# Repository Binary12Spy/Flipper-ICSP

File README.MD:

# Flipper-ICSP

Shout out to [Speexvocon](https://github.com/Speexvocon) for his [FlipperZeroKiCadPart](https://github.com/Speexvocon/FlipperZeroKiCadPart) making this project a whole lot easier!

I wanted to make a module for the Flipper Zero that works with [AVR Flasher](https://lab.flipper.net/apps/avr_isp) and simplifies hooking up a AVR microcontroller for flashing.  
This module simply formats the pins used by AVR Flasher into standard 10 position and 6 position ICSP headers with the option to choose between 3v3, 5v, or no supplied voltage.

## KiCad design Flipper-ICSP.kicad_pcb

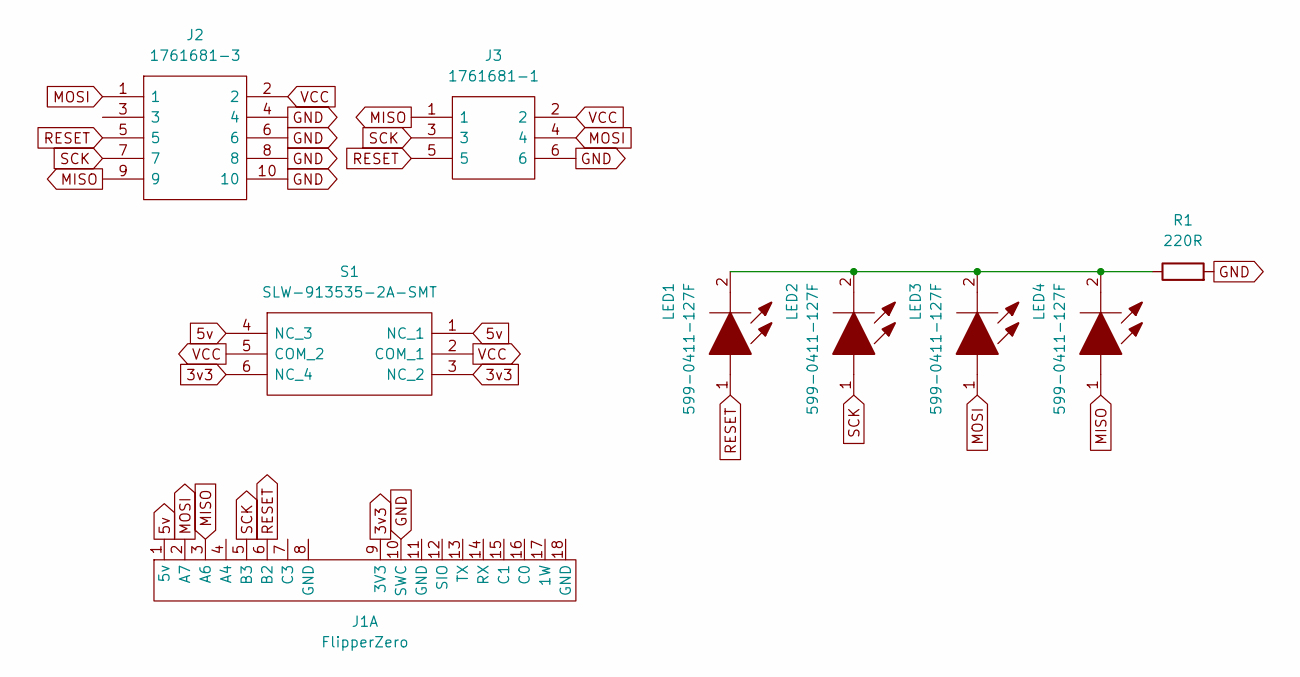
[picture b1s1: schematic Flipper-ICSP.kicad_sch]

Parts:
J1: FlipperZero; flipper zero through hole pins
J2: 1761681-3; SHDR10W67P254_2X5_2032X916X922P; Mouser Part Number 571-1761681-3
J3: 1761681-1; SHDR6W67P254_2X3_1524X916X922P; Mouser Part Number 571-1761681-1
LED1, LED2, LED3, LED4: 599-0411-127F; 5990411127F; Manufacturer_Part_Number 599-0411-127F
R1: 220R; R_1206_3216Metric_Pad1.30x1.75mm_HandSolder
S1: SLW-913535-2A-SMT; SLW9135352ASMT; Mouser Part Number 179-SLW-913535-2ASMT

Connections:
3v3: J1.9 (3V3), S1.3 (NC_2), S1.6 (NC_4)
5v: J1.1 (5v), S1.1 (NC_1), S1.4 (NC_3)
GND: J1.10 (SWC), J2.4, J2.6, J2.8, J2.10, J3.6, R1.2
MISO: J1.3 (A6), J2.9, J3.1, LED4.1
MOSI: J1.2 (A7), J2.1, J3.4, LED3.1
unnamed: LED1.2, LED2.2, LED3.2, LED4.2, R1.1
RESET: J1.6 (B2), J2.5, J3.5, LED1.1
SCK: J1.5 (B3), J2.7, J3.3, LED2.1
VCC: J2.2, J3.2, S1.2 (COM_1), S1.5 (COM_2)

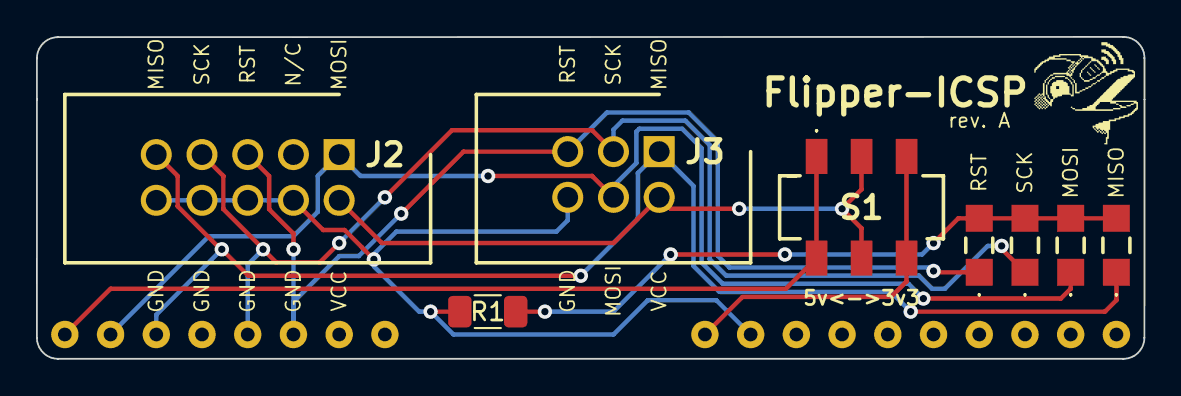
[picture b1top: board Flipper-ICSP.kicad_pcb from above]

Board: 2 copper layers, 61.5 x 17.9 mm, 9 parts (0 on the bottom side), 9 nets.

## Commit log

2024-01-07 Updated project layout
2024-01-07 Added readme
2024-01-07 Added Schematic and PCB renderings
2024-01-07 Removed backups
